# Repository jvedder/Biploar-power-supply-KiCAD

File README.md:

# Biploar-power-supply-KiCAD
A KiCAD PCB project for a simple linear bipolar power supply (+/-15V) from a 24V single-phase transformer.

This is a work in progress.  

MIT License

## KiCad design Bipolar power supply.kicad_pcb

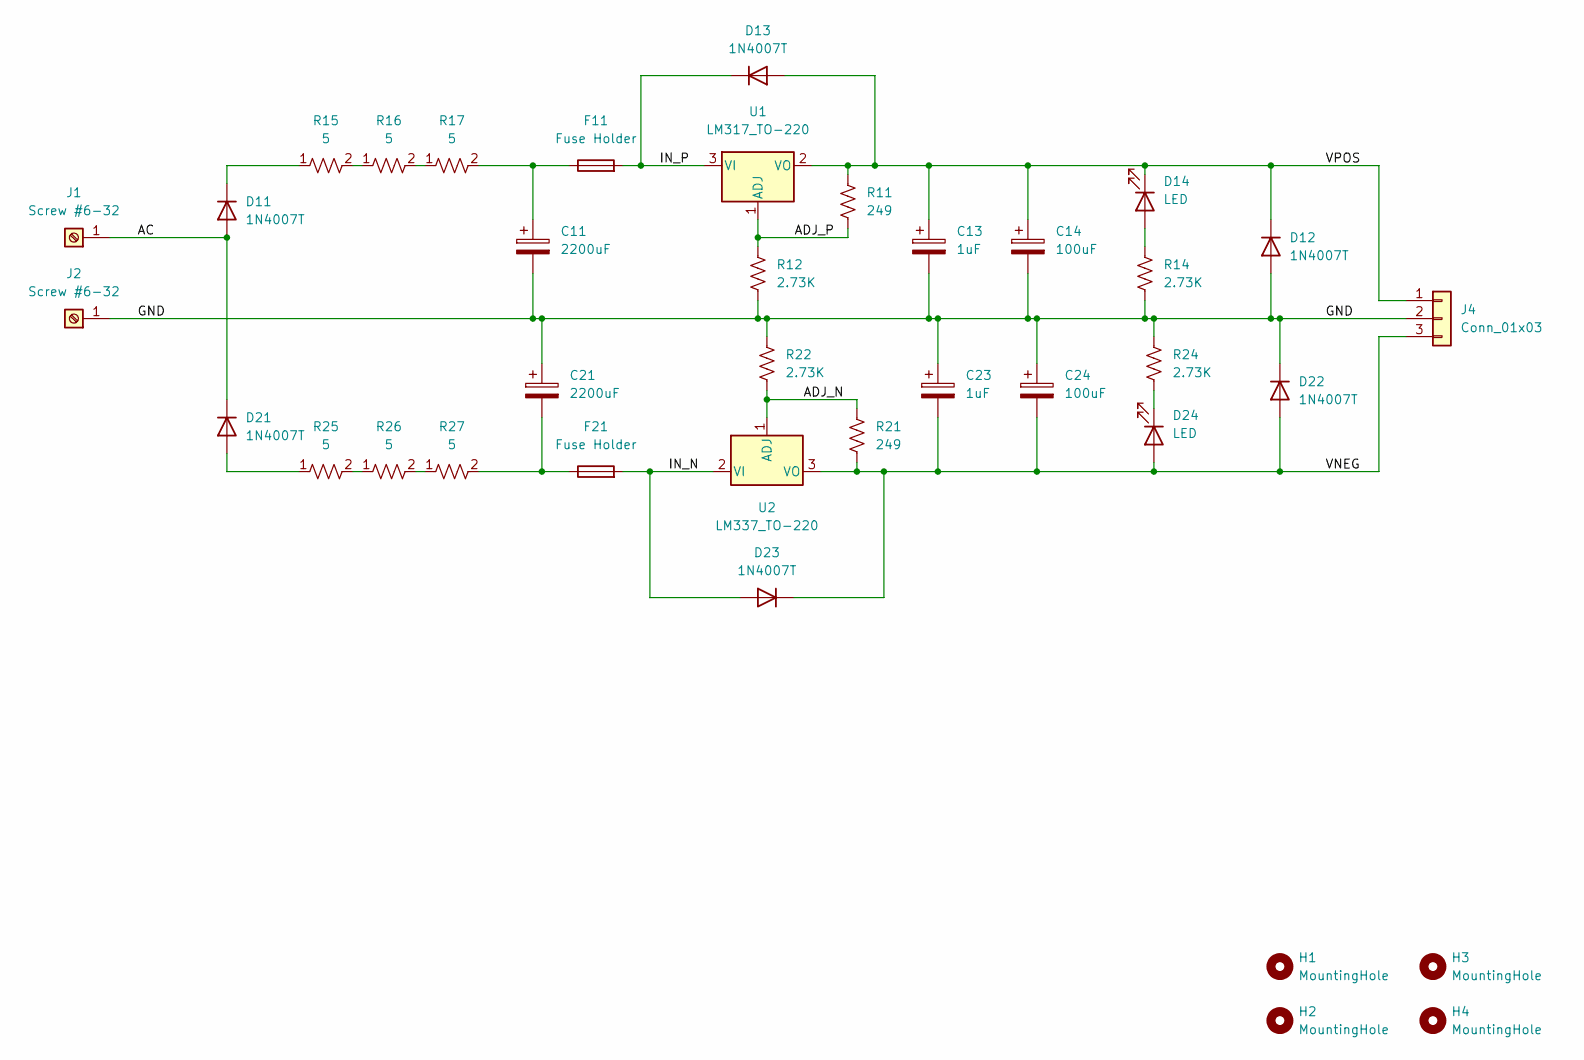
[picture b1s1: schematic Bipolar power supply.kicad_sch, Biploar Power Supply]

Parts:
C11, C21: 2200uF; CP_Radial_D16.0mm_P7.50mm
C13, C23: 1uF; CP_Radial_D5.0mm_P2.00mm
C14, C24: 100uF; CP_Radial_D10.0mm_P5.00mm
D11, D12, D13, D21, D22, D23: 1N4007T; D_DO-41_SOD81_P10.16mm_Horizontal
D14, D24: LED; LED_D5.0mm
F11, F21: Fuse Holder; FuseHolder_6.8x19.8mm_P3.4x13.5mm_Vetical
H1, H2, H3, H4: MountingHole; MountingHole_#6-32_Pad_10mm
J1, J2: Screw #6-32; ScrewTerminal_01x01_#6-32_10mm
J4: Conn_01x03; PinHeader_1x03_P2.54mm_Vertical
R11, R21: 249; R_0805_2012Metric_Pad1.20x1.40mm_HandSolder
R12, R14, R22, R24: 2.73K; R_0805_2012Metric_Pad1.20x1.40mm_HandSolder
R15, R16, R17, R25, R26, R27: 5; R_Axial_L13.1mm_D5.6mm_P20.0mm_Horizontal
U1: LM317_TO-220; TO-220-3_Vertical_Heatsink_19.1x9.7mm
U2: LM337_TO-220; TO-220-3_Vertical_Heatsink_19.1x9.7mm

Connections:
/AC: D11.2 (A), D21.1 (K), J1.1
/ADJ_N: R21.1, R22.2, U2.1 (ADJ)
/ADJ_P: R11.2, R12.1, U1.1 (ADJ)
/GND: C11.2, C13.2, C14.2, C21.1, C23.1, C24.1, D12.2 (A), D22.1 (K), J2.1, J4.2, R12.2, R14.2, R22.1, R24.1
/IN_N: D23.2 (A), F21.2, U2.2 (VI)
/IN_P: D13.1 (K), F11.2, U1.3 (VI)
/VNEG: C23.2, C24.2, D22.2 (A), D23.1 (K), D24.2 (A), J4.3, R21.2, U2.3 (VO)
/VPOS: C13.1, C14.1, D12.1 (K), D13.2 (A), D14.1 (K), J4.1, R11.1, U1.2 (VO)
unnamed: C11.1, F11.1, R17.2
unnamed: C21.2, F21.1, R27.2
unnamed: D14.2 (A), R14.1
unnamed: D24.1 (K), R24.2
unnamed: D11.1 (K), R15.1
unnamed: R15.2, R16.1
unnamed: R16.2, R17.1
unnamed: D21.2 (A), R25.1
unnamed: R25.2, R26.1
unnamed: R26.2, R27.1

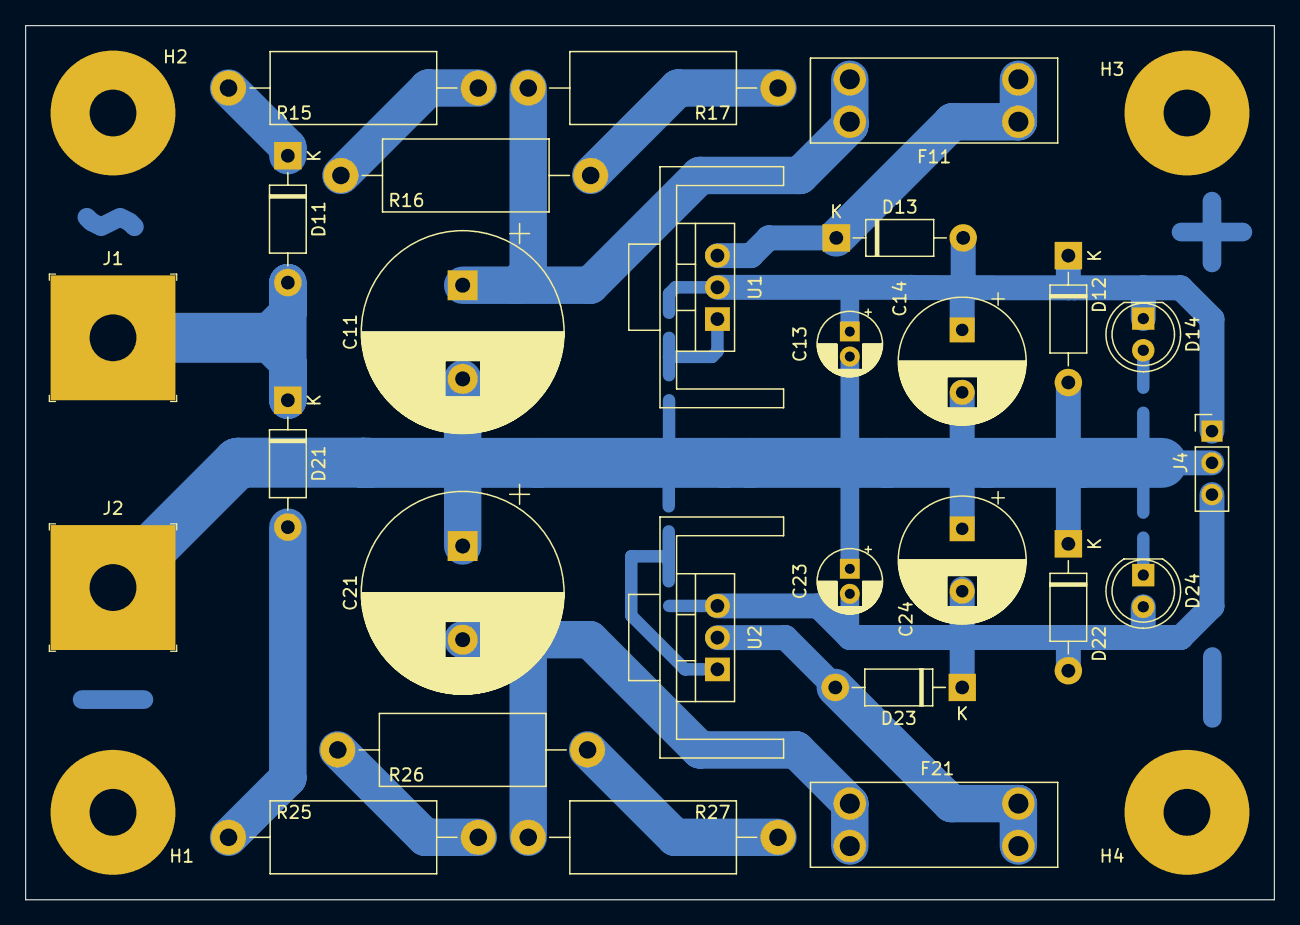
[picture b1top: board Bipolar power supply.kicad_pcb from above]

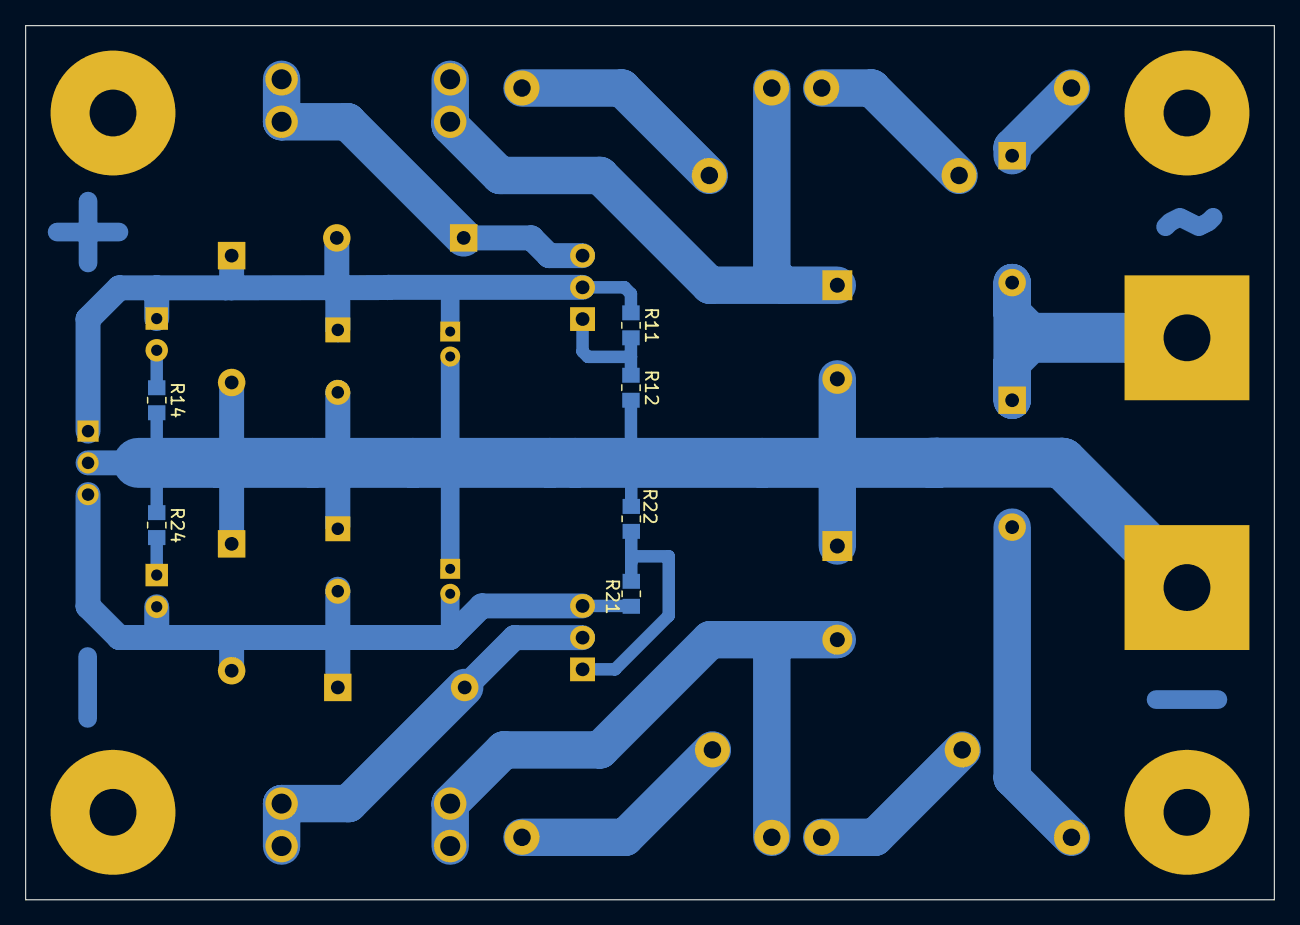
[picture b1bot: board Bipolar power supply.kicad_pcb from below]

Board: 2 copper layers, 100.0 x 70.0 mm, 37 parts (6 on the bottom side), 18 nets.

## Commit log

2023-01-07 Intial design
2023-01-07 Correct LICENSE and add README.md
2023-01-07 Added LTspice simulations
2023-01-08 Updated spice model
2023-01-08 Update spice parameters
2023-01-08 Update spice measurements for dropout voltage
2023-01-09 Revised schematic for (1) bridge rectifiers, (2) three power resistors, and (3) fuse holders.
2023-01-10 First pass at routing in 70x100 mm panel.
2023-01-10 Created footprint for TO-220 with Heatsink
2023-01-11 Routing WIP.
2023-01-14 Routing done. Used for dry fit.
2023-01-14 Updated footprints from dry fit.
2023-01-15 Added LEDs and edge clearance. Rerouted.
2023-01-15 Switched to non-CT transformer. Redesigned and rerouted.
2023-01-15 Created output fab and CNC files
2023-01-17 Add drill map
2023-01-18 Add autosave to .gitignore
2023-01-18 add hand-made CNC files for adding additional output connector and back plastic
2023-01-18 Remove more autosave files
2023-01-18 Update title blocks. Made PDFs

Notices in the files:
Bipolar power supply.kicad_pcb:
(C) 2023 John Vedder
